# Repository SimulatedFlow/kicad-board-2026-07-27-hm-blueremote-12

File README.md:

# 2026-07-27-hm-blueremote-12

<!-- SF-STORE-BLOCK:BEGIN -->
## 🛒 Source-available — see before you buy

This repository contains the **full design files** of a commercial hardware board. It is **source-available, not open source**: read it, evaluate it, then buy a license to use it. See **LICENSE.md (source-available, purchase required)**.

**Get it / Buy:**
- **Order on eBay** (this board, bare PCB): https://www.ebay.de/itm/398223886097
- Product page (specs, photos, price): https://simulatedflow.teufel-engineering.com/platinen/2026-07-27-hm-blueremote-12/
- eBay store — all our boards and PCB art: https://www.ebay.de/usr/simula-9
- Merch shop (dev & gaming): https://simulatedflow.myspreadshop.de
- Merch shop (Synthetica / EDM): https://synthetica.myspreadshop.de
- Direct / invoice (Simulated Flow UG): simulatedflow@gmail.com

### 📬 **Free Board Documentation & Firmware Pack**

Schematics, BOMs and example-firmware docs for our STM32 carrier boards. Get it by joining the newsletter — plus a heads-up when something new ships. Double opt-in, unsubscribe in one click, no address sharing.

👉 **[Get the free pack](https://simulatedflow.teufel-engineering.com/newsletter/hardware/?q=gh)**

_© 2026 Simulated Flow UG. All rights reserved._
<!-- SF-STORE-BLOCK:END -->

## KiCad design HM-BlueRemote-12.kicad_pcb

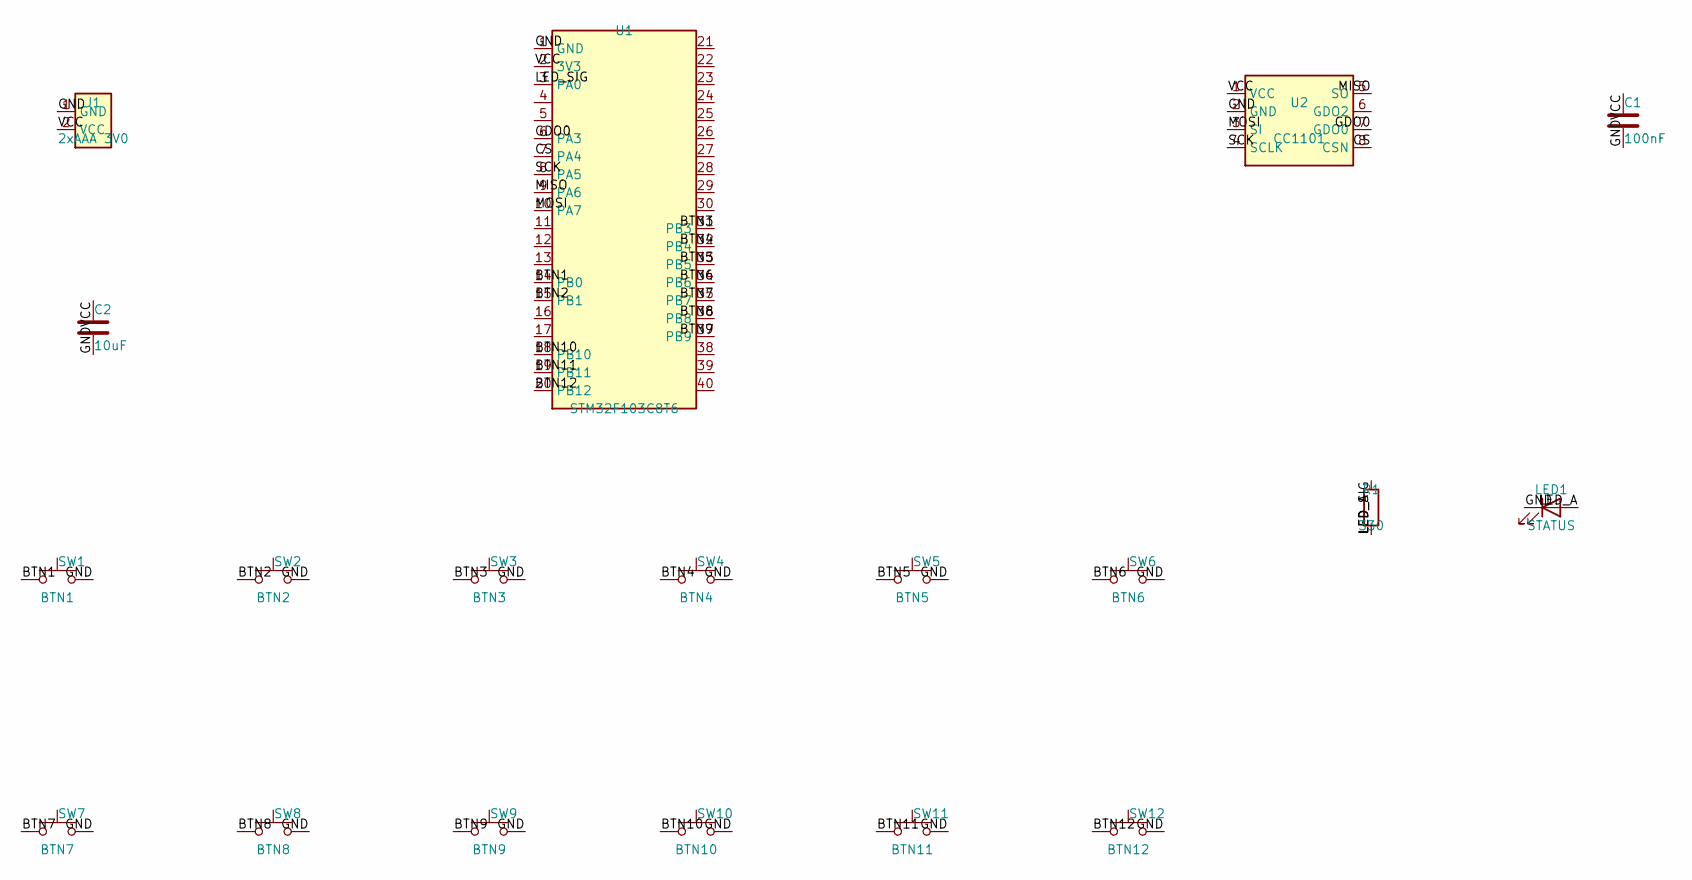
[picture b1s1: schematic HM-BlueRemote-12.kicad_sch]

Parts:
C1: 100nF; C_0805_2012Metric
C2: 10uF; C_1206_3216Metric
J1: 2xAAA 3V0; JST_PH_B2B-PH-K_1x02_P2.00mm_Vertical
LED1: STATUS; LED_0805_2012Metric
R1: 330; R_0805_2012Metric
SW1: BTN1; SW_SPST_PTS645Sx43SMTR92
SW2: BTN2; SW_SPST_PTS645Sx43SMTR92
SW3: BTN3; SW_SPST_PTS645Sx43SMTR92
SW4: BTN4; SW_SPST_PTS645Sx43SMTR92
SW5: BTN5; SW_SPST_PTS645Sx43SMTR92
SW6: BTN6; SW_SPST_PTS645Sx43SMTR92
SW7: BTN7; SW_SPST_PTS645Sx43SMTR92
SW8: BTN8; SW_SPST_PTS645Sx43SMTR92
SW9: BTN9; SW_SPST_PTS645Sx43SMTR92
SW10: BTN10; SW_SPST_PTS645Sx43SMTR92
SW11: BTN11; SW_SPST_PTS645Sx43SMTR92
SW12: BTN12; SW_SPST_PTS645Sx43SMTR92
U1: STM32F103C8T6; Bluepill_Socket_2x20
U2: CC1101; PinSocket_2x04_P2.54mm_Vertical

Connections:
BTN1: SW1.1, U1.14 (PB0)
BTN2: SW2.1, U1.15 (PB1)
BTN3: SW3.1, U1.31 (PB3)
BTN4: SW4.1, U1.32 (PB4)
BTN5: SW5.1, U1.33 (PB5)
BTN6: SW6.1, U1.34 (PB6)
BTN7: SW7.1, U1.35 (PB7)
BTN8: SW8.1, U1.36 (PB8)
BTN9: SW9.1, U1.37 (PB9)
BTN10: SW10.1, U1.18 (PB10)
BTN11: SW11.1, U1.19 (PB11)
BTN12: SW12.1, U1.20 (PB12)
CS: U1.7 (PA4), U2.8 (CSN)
GDO0: U1.6 (PA3), U2.7 (GDO0)
GND: C1.2, C2.2, J1.1 (GND), LED1.1 (K), SW1.2, SW2.2, SW3.2, SW4.2, SW5.2, SW6.2, SW7.2, SW8.2, SW9.2, SW10.2, SW11.2, SW12.2, U1.1 (GND), U2.2 (GND)
LED_A: LED1.2 (A), R1.2
LED_SIG: R1.1, U1.3 (PA0)
MISO: U1.9 (PA6), U2.5 (SO)
MOSI: U1.10 (PA7), U2.3 (SI)
SCK: U1.8 (PA5), U2.4 (SCLK)
VCC: C1.1, C2.1, J1.2 (VCC), U1.2 (3V3), U2.1 (VCC)

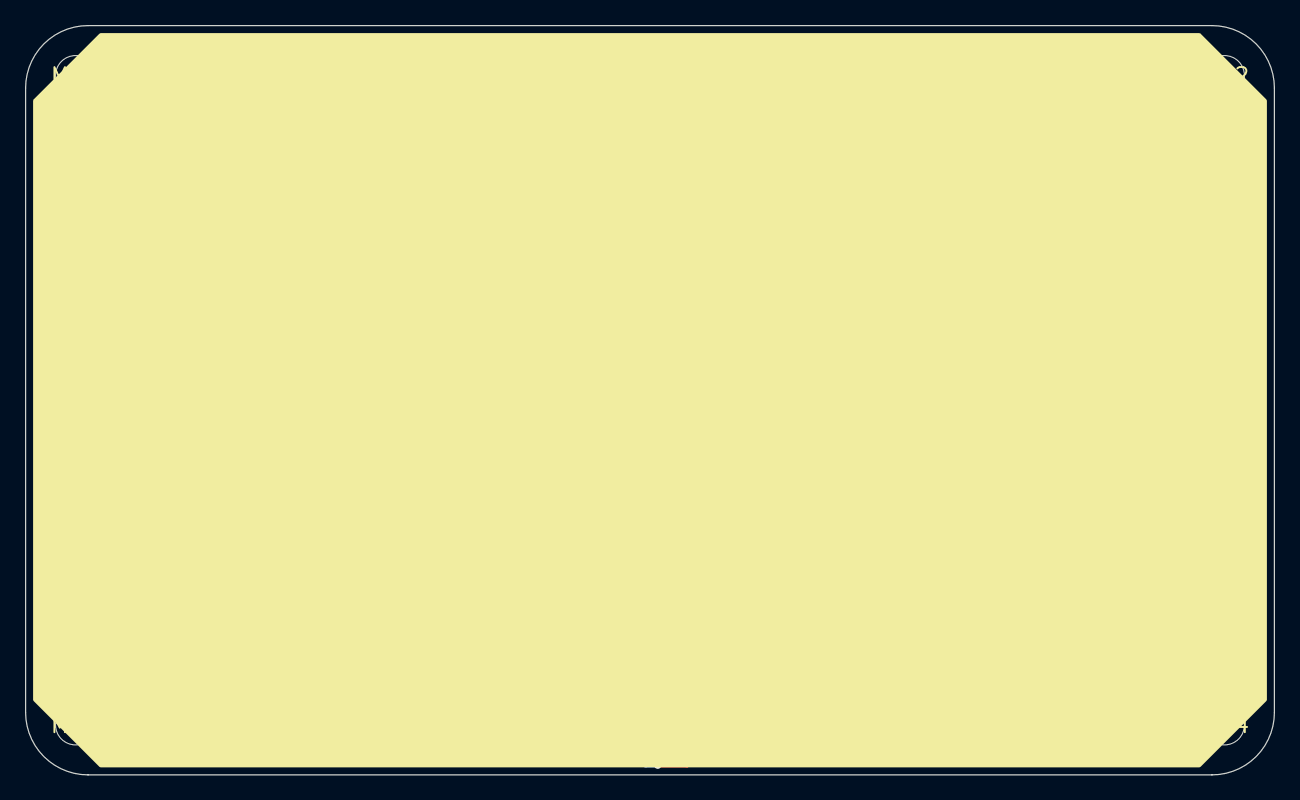
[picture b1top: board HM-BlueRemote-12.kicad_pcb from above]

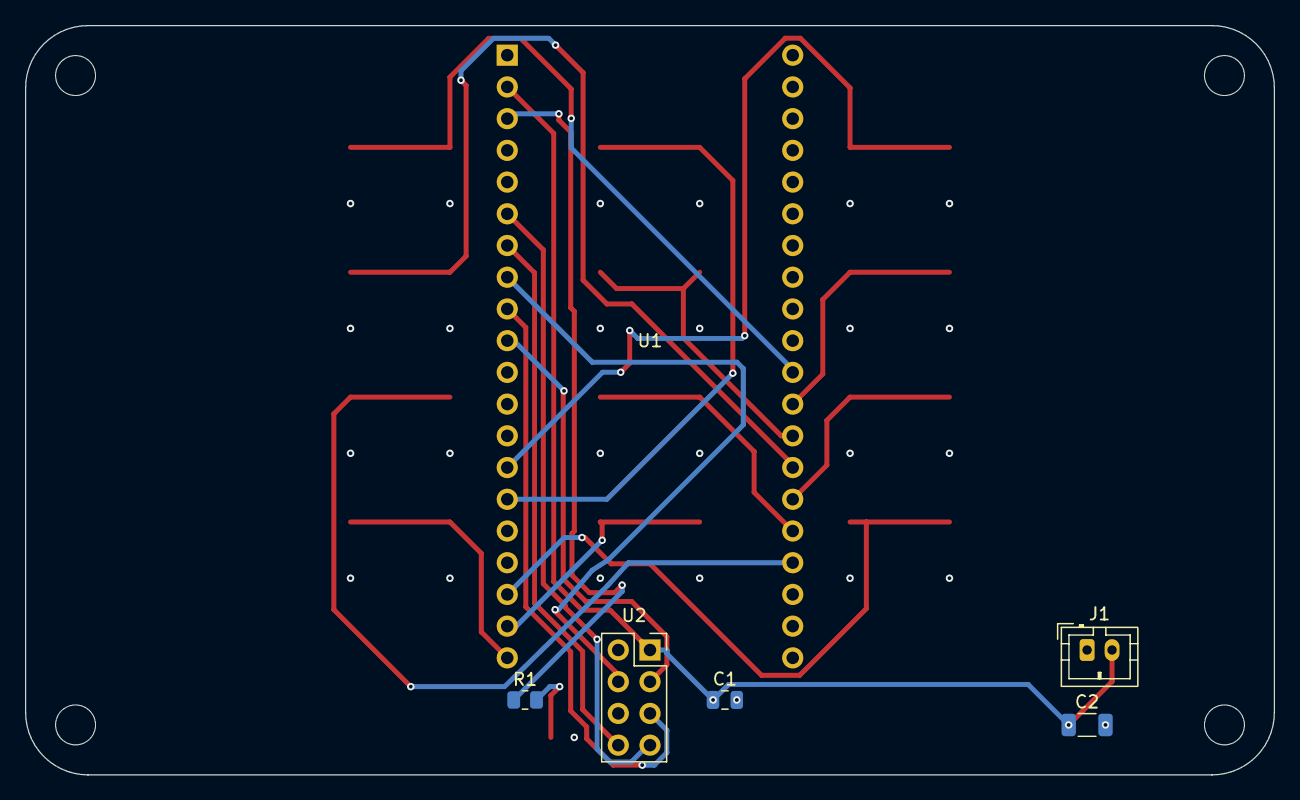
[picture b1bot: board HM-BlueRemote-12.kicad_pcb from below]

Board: 4 copper layers, 100.0 x 60.0 mm, 23 parts (6 on the bottom side), 21 nets.

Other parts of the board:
MH1, MH2, MH3, MH4: MountingHole_3.2mm

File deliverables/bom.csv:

"Refs","Value","Footprint","Qty","DNP"
"C1","100nF","Capacitor_SMD:C_0805_2012Metric","1",""
"C2","10uF","Capacitor_SMD:C_1206_3216Metric","1",""
"J1","2xAAA 3V0","Connector_JST:JST_PH_B2B-PH-K_1x02_P2.00mm_Vertical","1",""
"LED1","STATUS","LED_SMD:LED_0805_2012Metric","1",""
"R1","330","Resistor_SMD:R_0805_2012Metric","1",""
"SW1","BTN1","Button_Switch_SMD:SW_SPST_PTS645Sx43SMTR92","1",""
"SW2","BTN2","Button_Switch_SMD:SW_SPST_PTS645Sx43SMTR92","1",""
"SW3","BTN3","Button_Switch_SMD:SW_SPST_PTS645Sx43SMTR92","1",""
"SW4","BTN4","Button_Switch_SMD:SW_SPST_PTS645Sx43SMTR92","1",""
"SW5","BTN5","Button_Switch_SMD:SW_SPST_PTS645Sx43SMTR92","1",""
"SW6","BTN6","Button_Switch_SMD:SW_SPST_PTS645Sx43SMTR92","1",""
"SW7","BTN7","Button_Switch_SMD:SW_SPST_PTS645Sx43SMTR92","1",""
"SW8","BTN8","Button_Switch_SMD:SW_SPST_PTS645Sx43SMTR92","1",""
"SW9","BTN9","Button_Switch_SMD:SW_SPST_PTS645Sx43SMTR92","1",""
"SW10","BTN10","Button_Switch_SMD:SW_SPST_PTS645Sx43SMTR92","1",""
"SW11","BTN11","Button_Switch_SMD:SW_SPST_PTS645Sx43SMTR92","1",""
"SW12","BTN12","Button_Switch_SMD:SW_SPST_PTS645Sx43SMTR92","1",""
"U1","STM32F103C8T6","HM-BlueRemote-12:Bluepill_Socket_2x20","1",""
"U2","CC1101","Connector_PinSocket_2.54mm:PinSocket_2x04_P2.54mm_Vertical","1",""
